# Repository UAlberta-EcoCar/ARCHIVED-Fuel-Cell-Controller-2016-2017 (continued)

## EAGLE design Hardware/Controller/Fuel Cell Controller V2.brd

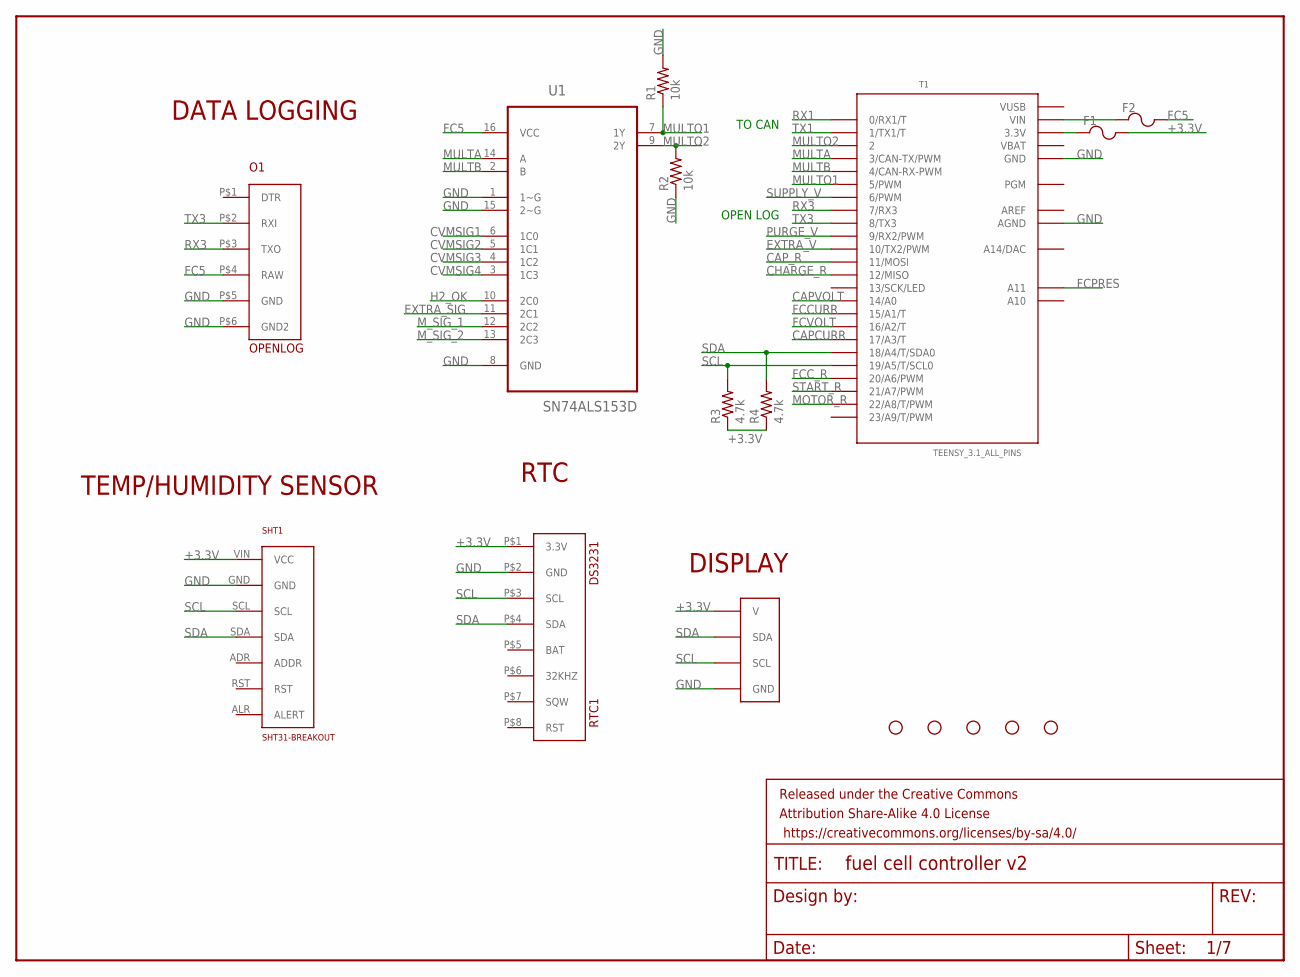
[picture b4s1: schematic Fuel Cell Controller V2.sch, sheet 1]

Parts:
F1, F2: POLYFUSE; 1206
FRAME1: FRAME-LETTERNO_PACKAGE; DUMMY
LCD1: LCD-BOARD
O1: OPENLOG
R1, R2: 10k; 0805
R3, R4: 4.7k; 0805
RTC1: DS3231
SHT1: SHT31-BREAKOUT
STANDOFF1, STANDOFF2, STANDOFF3, STANDOFF4, STANDOFF5: STAND-OFF
T1: TEENSY_3.1_ALL_PINS; TEENSY3-ALL_PINS
U1: SN74ALS153D; SOIC127P600X175-16N

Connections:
+3.3V: F1.2, LCD1.V, R3.1, R4.1, RTC1.P$1 (3.3V), SHT1.VIN (VCC); also elsewhere on the board
AREF: T1.AREF
CAPCURR: T1.17/A3 (17/A3/T); also elsewhere on the board
CAPVOLT: T1.14/A0; also elsewhere on the board
CAP_R: T1.11 (11/MOSI); also elsewhere on the board
CHARGE_R: T1.12 (12/MISO); also elsewhere on the board
CVMSIG1: U1.6 (1C0); also elsewhere on the board
CVMSIG2: U1.5 (1C1); also elsewhere on the board
CVMSIG3: U1.4 (1C2); also elsewhere on the board
CVMSIG4: U1.3 (1C3); also elsewhere on the board
EXTRA_SIG: U1.11 (2C1); also elsewhere on the board
EXTRA_V: T1.10 (10/TX2/PWM); also elsewhere on the board
FC5: F2.2, O1.P$4 (RAW), U1.16 (VCC); also elsewhere on the board
FCCURR: T1.15/A1 (15/A1/T); also elsewhere on the board
FCC_R: T1.20/A6 (20/A6/PWM); also elsewhere on the board
FCPRES: T1.A11; also elsewhere on the board
FCVOLT: T1.16/A2 (16/A2/T); also elsewhere on the board
GND: LCD1.GND1 (GND), LCD1.GND2 (GND), LCD1.GND3 (GND), LCD1.GND4 (GND), LCD1.GND5 (GND), LCD1.GND6 (GND), LCD1.GND7 (GND), LCD1.GND8 (GND), LCD1.GND9 (GND), LCD1.GND10 (GND), LCD1.GND11 (GND), LCD1.GND12 (GND), LCD1.GND13 (GND), O1.P$5 (GND), O1.P$6 (GND2), R1.2, R2.1, RTC1.P$2 (GND), SHT1.GND, T1.AGND, T1.GND, T1.GND1 (GND), U1.1 (1~G), U1.8 (GND), U1.15 (2~G); also elsewhere on the board
H2_OK: U1.10 (2C0); also elsewhere on the board
MOTOR_R: T1.22/A8 (22/A8/T/PWM); also elsewhere on the board
MULTA: T1.3 (3/CAN-TX/PWM), U1.14 (A)
MULTB: T1.4 (4/CAN-RX-PWM), U1.2 (B)
MULTO1: R1.1, T1.5 (5/PWM), U1.7 (1Y)
MULTO2: R2.2, T1.2, U1.9 (2Y)
M_SIG_1: U1.12 (2C2); also elsewhere on the board
M_SIG_2: U1.13 (2C3); also elsewhere on the board
unnamed: F2.1, T1.VIN
unnamed: F1.1, T1.3.3V, T1.3.3V1 (3.3V)
PURGE_V: T1.9 (9/RX2/PWM); also elsewhere on the board
RX1: T1.0 (0/RX1/T); also elsewhere on the board
RX3: O1.P$3 (TXO), T1.7 (7/RX3)
SCL: LCD1.SCL, R3.2, RTC1.P$3 (SCL), SHT1.SCL, T1.19/A5 (19/A5/T/SCL0); also elsewhere on the board
SDA: LCD1.SDA, R4.2, RTC1.P$4 (SDA), SHT1.SDA, T1.18/A4 (18/A4/T/SDA0); also elsewhere on the board
START_R: T1.21/A7 (21/A7/PWM); also elsewhere on the board
SUPPLY_V: T1.6 (6/PWM); also elsewhere on the board
TX1: T1.1 (1/TX1/T); also elsewhere on the board
TX3: O1.P$2 (RXI), T1.8 (8/TX3)
VBAT: T1.VBAT
VUSB: T1.VUSB

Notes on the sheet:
TO CAN
OPEN LOG
DISPLAY
DATA LOGGING
TEMP/HUMIDITY SENSOR
RTC

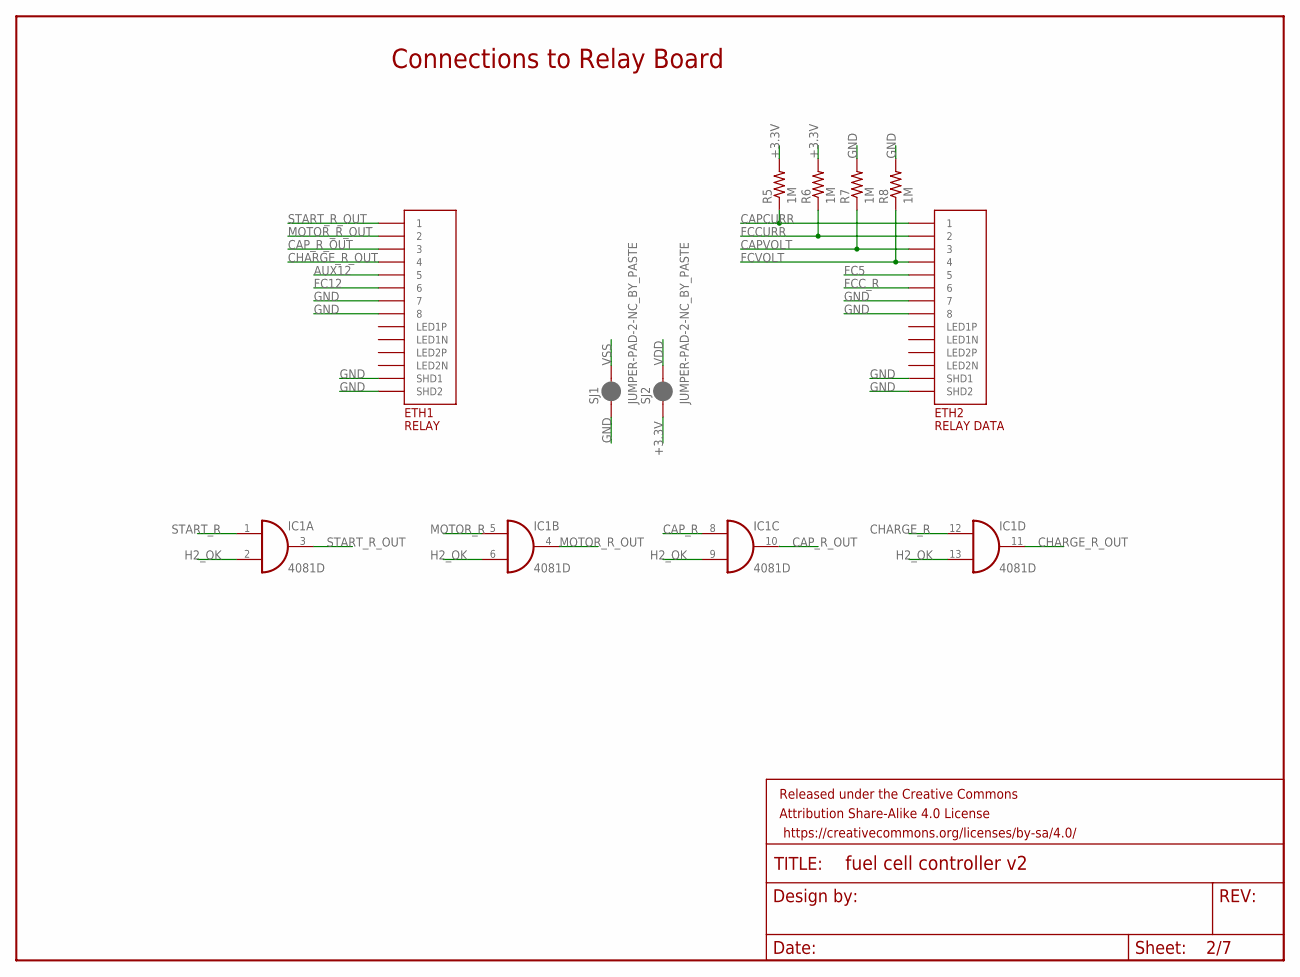
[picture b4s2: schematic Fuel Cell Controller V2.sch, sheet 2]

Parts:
ETH1: RELAY; A122645-ND
ETH2: RELAY DATA; A122645-ND
FRAME2: FRAME-LETTERNO_PACKAGE; DUMMY
IC1: 4081D; SO14
R5, R6, R7, R8: 1M; 0805
SJ1, SJ2: JUMPER-PAD-2-NC_BY_PASTE; PAD-JUMPER-2-NC_BY_PASTE_YES_SILK

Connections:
+3.3V: R5.2, R6.2, SJ2.1; also elsewhere on the board
AUX12: ETH1.P$5 (5); also elsewhere on the board
CAPCURR: ETH2.P$1 (1), R5.1; also elsewhere on the board
CAPVOLT: ETH2.P$3 (3), R7.1; also elsewhere on the board
CAP_R: IC1.8 (I0); also elsewhere on the board
CAP_R_OUT: ETH1.P$3 (3), IC1.10 (O)
CHARGE_R: IC1.12 (I0); also elsewhere on the board
CHARGE_R_OUT: ETH1.P$4 (4), IC1.11 (O)
FC5: ETH2.P$5 (5); also elsewhere on the board
FC12: ETH1.P$6 (6); also elsewhere on the board
FCCURR: ETH2.P$2 (2), R6.1; also elsewhere on the board
FCC_R: ETH2.P$6 (6); also elsewhere on the board
FCVOLT: ETH2.P$4 (4), R8.1; also elsewhere on the board
GND: ETH1.P$7 (7), ETH1.P$8 (8), ETH1.P$13 (SHD1), ETH1.P$14 (SHD2), ETH2.P$7 (7), ETH2.P$8 (8), ETH2.P$13 (SHD1), ETH2.P$14 (SHD2), R7.2, R8.2, SJ1.1; also elsewhere on the board
H2_OK: IC1.2 (I1), IC1.6 (I1), IC1.9 (I1), IC1.13 (I1); also elsewhere on the board
MOTOR_R: IC1.5 (I0); also elsewhere on the board
MOTOR_R_OUT: ETH1.P$2 (2), IC1.4 (O)
START_R: IC1.1 (I0); also elsewhere on the board
START_R_OUT: ETH1.P$1 (1), IC1.3 (O)
VDD: IC1.14 (VDD), SJ2.2
VSS: IC1.7 (VSS), SJ1.2

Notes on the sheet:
Connections to Relay Board

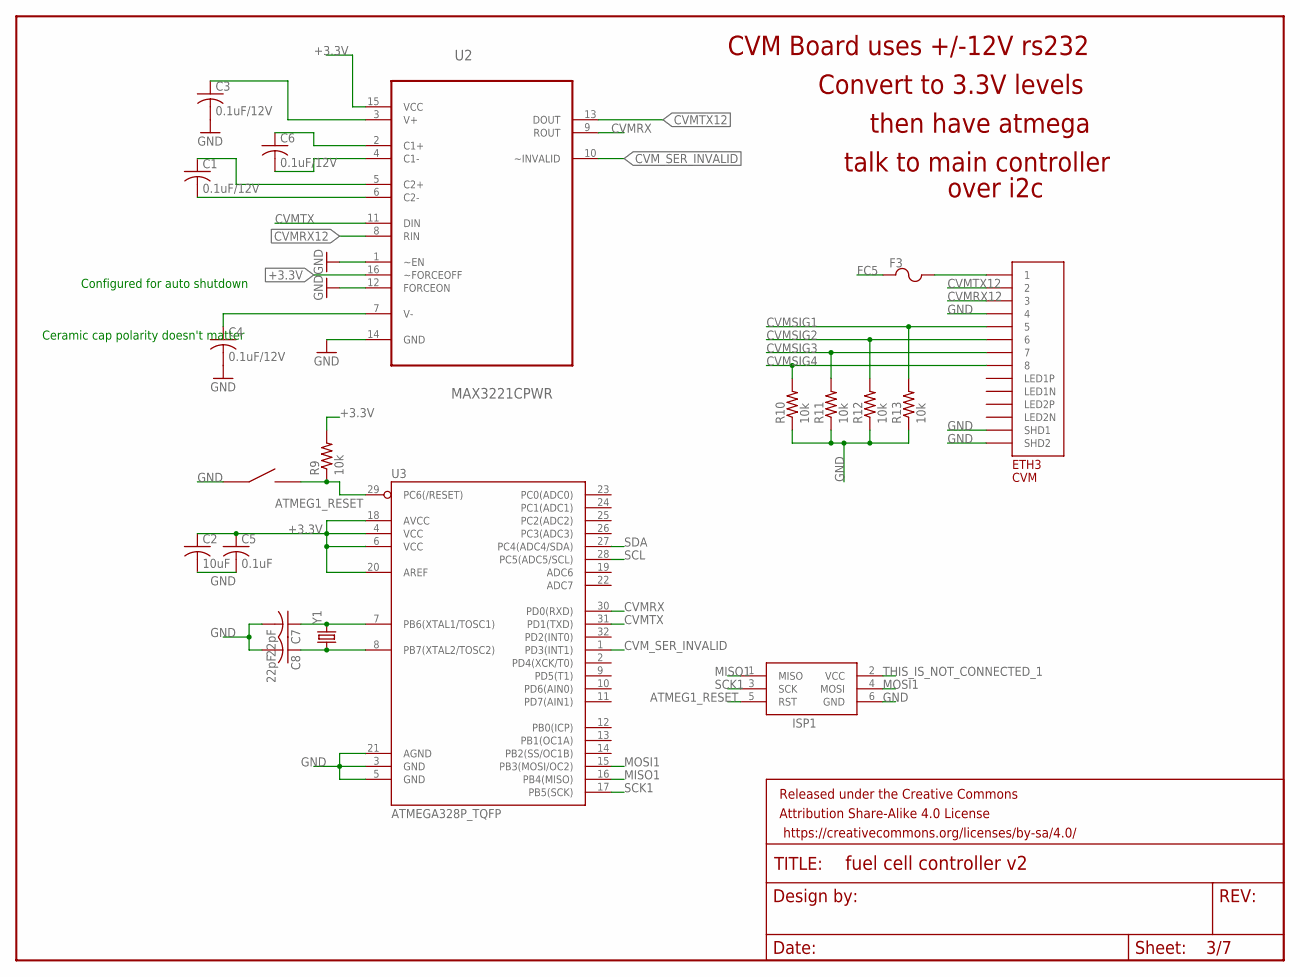
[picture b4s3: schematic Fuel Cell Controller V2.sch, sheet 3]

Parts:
C1, C3, C4, C6: 0.1uF/12V; C0805
C2: 10uF; C0603
C5: 0.1uF; C0603
C7, C8: 22pF; C0603
ETH3: CVM; A122645-ND
F3: POLYFUSE; 1206
FRAME3: FRAME-LETTERNO_PACKAGE; DUMMY
ISP1: AVRISP-BOX
R9: 10k; R0603
R10, R11, R12, R13: 10k; 0805
S1: EG4621CT-ND
U2: MAX3221CPWR; SOP65P640X120-16N
U3: ATMEGA328P_TQFP; TQFP32-08
Y1: CRYSTALHC49US; HC49US

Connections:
+3.3V: C2.1, C5.1, R9.2, U2.15 (VCC), U2.16 (~FORCEOFF), U3.4 (VCC), U3.6 (VCC), U3.18 (AVCC), U3.20 (AREF); also elsewhere on the board
ATMEG1_RESET: ISP1.5 (RST), R9.1, S1.P$3, S1.P$4, U3.29 (PC6(/RESET))
CVMRX: U2.9 (ROUT), U3.30 (PD0(RXD))
CVMRX12: ETH3.P$3 (3), U2.8 (RIN)
CVMSIG1: ETH3.P$5 (5), R13.2; also elsewhere on the board
CVMSIG2: ETH3.P$6 (6), R12.2; also elsewhere on the board
CVMSIG3: ETH3.P$7 (7), R11.2; also elsewhere on the board
CVMSIG4: ETH3.P$8 (8), R10.2; also elsewhere on the board
CVMTX: U2.11 (DIN), U3.31 (PD1(TXD))
CVMTX12: ETH3.P$2 (2), U2.13 (DOUT)
CVM_SER_INVALID: U2.10 (~INVALID), U3.1 (PD3(INT1))
FC5: F3.1; also elsewhere on the board
GND: C2.2, C3.2, C4.2, C5.2, C7.2, C8.2, ETH3.P$4 (4), ETH3.P$13 (SHD1), ETH3.P$14 (SHD2), ISP1.6 (GND), R10.1, R11.1, R12.1, R13.1, S1.P$1, S1.P$2, U2.1 (~EN), U2.12 (FORCEON), U2.14 (GND), U3.3 (GND), U3.5 (GND), U3.21 (AGND); also elsewhere on the board
MISO1: ISP1.1 (MISO), U3.16 (PB4(MISO))
MOSI1: ISP1.4 (MOSI), U3.15 (PB3(MOSI/OC2))
unnamed: C7.1, U3.7 (PB6(XTAL1/TOSC1)), Y1.2
unnamed: C8.1, U3.8 (PB7(XTAL2/TOSC2)), Y1.1
unnamed: ETH3.P$1 (1), F3.2
unnamed: C3.1, U2.3 (V+)
unnamed: C6.1, U2.2 (C1+)
unnamed: C6.2, U2.4 (C1-)
unnamed: C1.1, U2.5 (C2+)
unnamed: C1.2, U2.6 (C2-)
unnamed: C4.1, U2.7 (V-)
SCK1: ISP1.3 (SCK), U3.17 (PB5(SCK))
SCL: U3.28 (PC5(ADC5/SCL)); also elsewhere on the board
SDA: U3.27 (PC4(ADC4/SDA)); also elsewhere on the board
THIS_IS_NOT_CONNECTED_1: ISP1.2 (VCC)

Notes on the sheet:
Configured for auto shutdown
CVM Board uses +/-12V rs232
Convert to 3.3V levels
then have atmega
talk to main controller
over i2c
Ceramic cap polarity doesn't matter

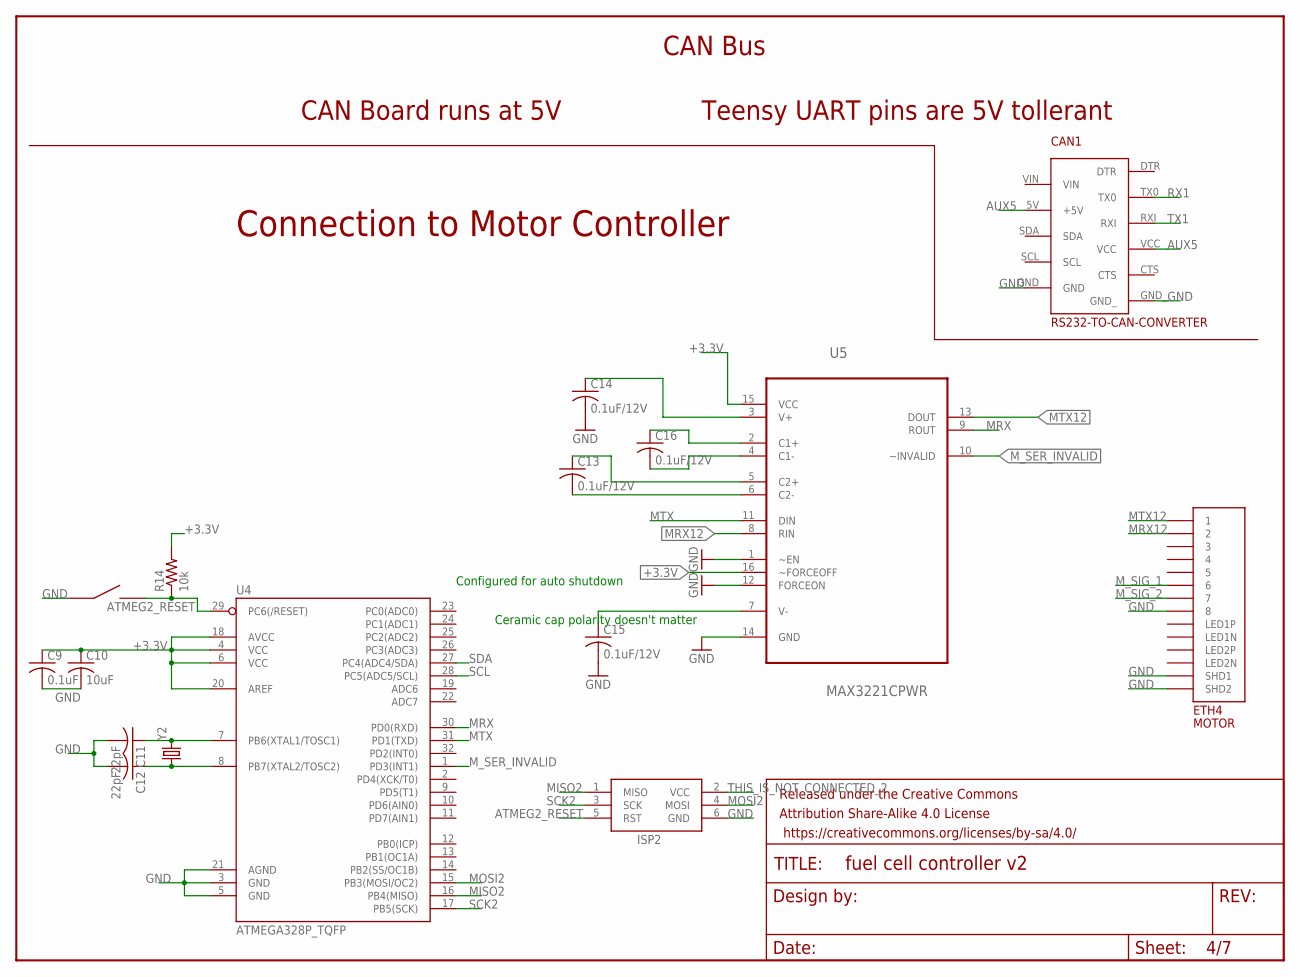
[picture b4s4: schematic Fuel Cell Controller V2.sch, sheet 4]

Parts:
C9: 0.1uF; C0603
C10: 10uF; C0603
C11, C12: 22pF; C0603
C13, C14, C15, C16: 0.1uF/12V; C0805
CAN1: RS232-TO-CAN-CONVERTER
ETH4: MOTOR; A122645-ND
FRAME4: FRAME-LETTERNO_PACKAGE; DUMMY
ISP2: AVRISP-BOX
R14: 10k; R0603
S2: EG4621CT-ND
U4: ATMEGA328P_TQFP; TQFP32-08
U5: MAX3221CPWR; SOP65P640X120-16N
Y2: CRYSTALHC49US; HC49US

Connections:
+3.3V: C9.1, C10.1, R14.2, U4.4 (VCC), U4.6 (VCC), U4.18 (AVCC), U4.20 (AREF), U5.15 (VCC), U5.16 (~FORCEOFF); also elsewhere on the board
ATMEG2_RESET: ISP2.5 (RST), R14.1, S2.P$3, S2.P$4, U4.29 (PC6(/RESET))
AUX5: CAN1.5V (+5V), CAN1.VCC; also elsewhere on the board
GND: C9.2, C10.2, C11.2, C12.2, C14.2, C15.2, CAN1.GND, CAN1.GND_, ETH4.P$8 (8), ETH4.P$13 (SHD1), ETH4.P$14 (SHD2), ISP2.6 (GND), S2.P$1, S2.P$2, U4.3 (GND), U4.5 (GND), U4.21 (AGND), U5.1 (~EN), U5.12 (FORCEON), U5.14 (GND); also elsewhere on the board
MISO2: ISP2.1 (MISO), U4.16 (PB4(MISO))
MOSI2: ISP2.4 (MOSI), U4.15 (PB3(MOSI/OC2))
MRX: U4.30 (PD0(RXD)), U5.9 (ROUT)
MRX12: ETH4.P$2 (2), U5.8 (RIN)
MTX: U4.31 (PD1(TXD)), U5.11 (DIN)
MTX12: ETH4.P$1 (1), U5.13 (DOUT)
M_SER_INVALID: U4.1 (PD3(INT1)), U5.10 (~INVALID)
M_SIG_1: ETH4.P$6 (6); also elsewhere on the board
M_SIG_2: ETH4.P$7 (7); also elsewhere on the board
unnamed: C11.1, U4.7 (PB6(XTAL1/TOSC1)), Y2.2
unnamed: C12.1, U4.8 (PB7(XTAL2/TOSC2)), Y2.1
unnamed: C14.1, U5.3 (V+)
unnamed: C16.1, U5.2 (C1+)
unnamed: C16.2, U5.4 (C1-)
unnamed: C13.1, U5.5 (C2+)
unnamed: C13.2, U5.6 (C2-)
unnamed: C15.1, U5.7 (V-)
RX1: CAN1.TX0; also elsewhere on the board
SCK2: ISP2.3 (SCK), U4.17 (PB5(SCK))
SCL: U4.28 (PC5(ADC5/SCL)); also elsewhere on the board
SDA: U4.27 (PC4(ADC4/SDA)); also elsewhere on the board
THIS_IS_NOT_CONNECTED_2: ISP2.2 (VCC)
TX1: CAN1.RXI; also elsewhere on the board

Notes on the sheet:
CAN Bus
CAN Board runs at 5V
Teensy UART pins are 5V tollerant
Connection to Motor Controller
Configured for auto shutdown
Ceramic cap polarity doesn't matter

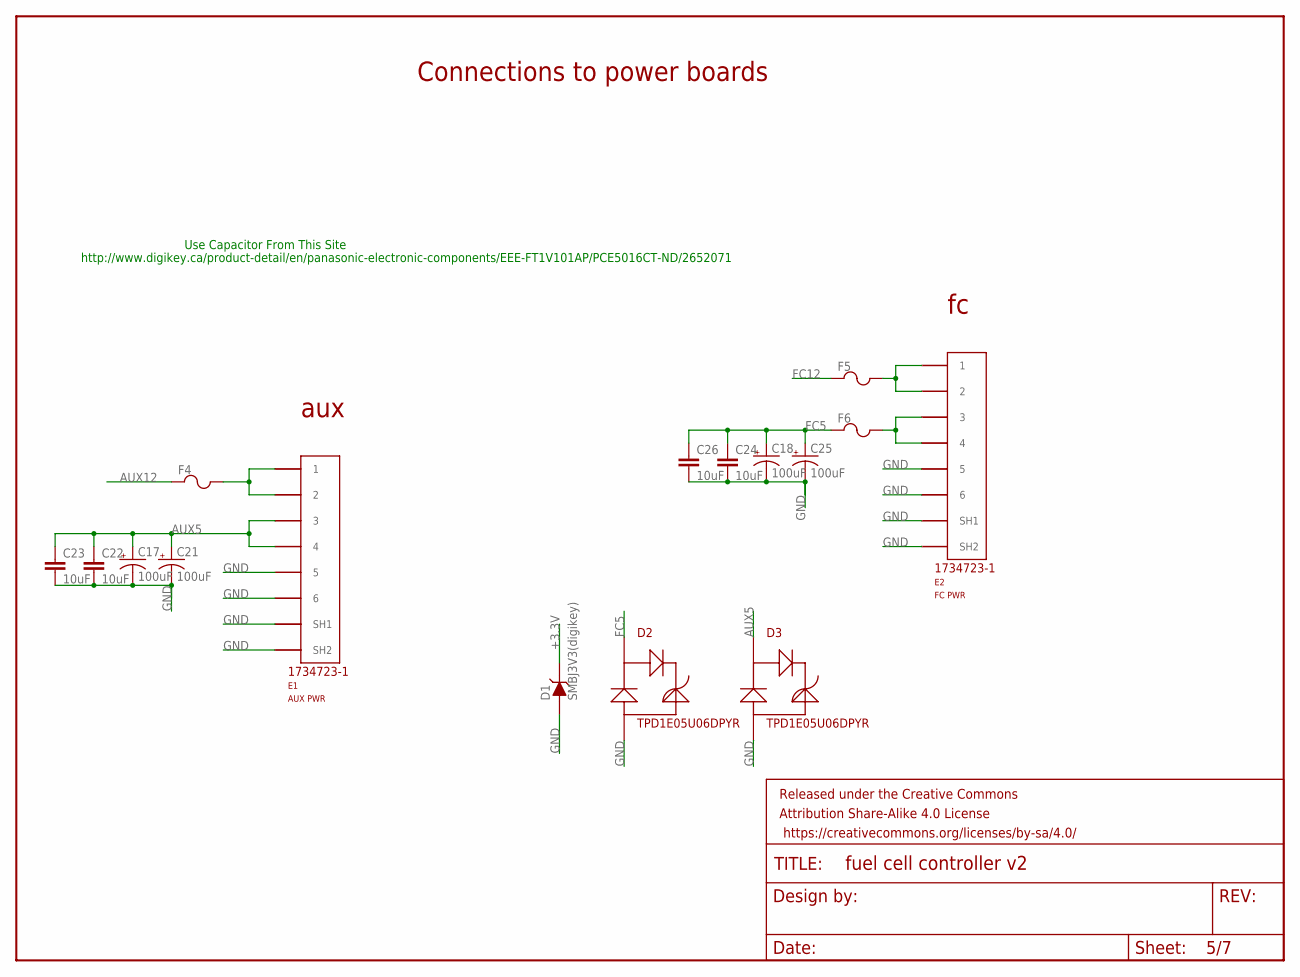
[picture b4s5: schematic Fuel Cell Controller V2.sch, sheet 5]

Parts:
C17, C18, C21, C25: 100uF; PANASONIC_D
C22, C23, C24, C26: 10uF; 0805
D1: SMBJ3V3(digikey); DO-214AB
D2, D3: TPD1E05U06DPYR; 2-XDFN
E1: AUX PWR; 1734723-1_RJ11
E2: FC PWR; 1734723-1_RJ11
F4, F5, F6: POLYFUSE; 1206
FRAME5: FRAME-LETTERNO_PACKAGE; DUMMY

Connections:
+3.3V: D1.C; also elsewhere on the board
AUX5: C17.+, C21.+, C22.1, C23.1, D3.P$1, E1.3, E1.4; also elsewhere on the board
AUX12: F4.1; also elsewhere on the board
FC5: C18.+, C24.1, C25.+, C26.1, D2.P$1, F6.1; also elsewhere on the board
FC12: F5.1; also elsewhere on the board
GND: C17.-, C18.-, C21.-, C22.2, C23.2, C24.2, C25.-, C26.2, D1.A, D2.P$2, D3.P$2, E1.5, E1.6, E1.SH1, E1.SH2, E2.5, E2.6, E2.SH1, E2.SH2; also elsewhere on the board
unnamed: E1.1, E1.2, F4.2
unnamed: E2.1, E2.2, F5.2
unnamed: E2.3, E2.4, F6.2

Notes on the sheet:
Connections to power boards
aux
Use Capacitor From This Site
http://www.digikey.ca/product-detail/en/panasonic-electronic-components/EEE-FT1V101AP/PCE5016CT-ND/2652071

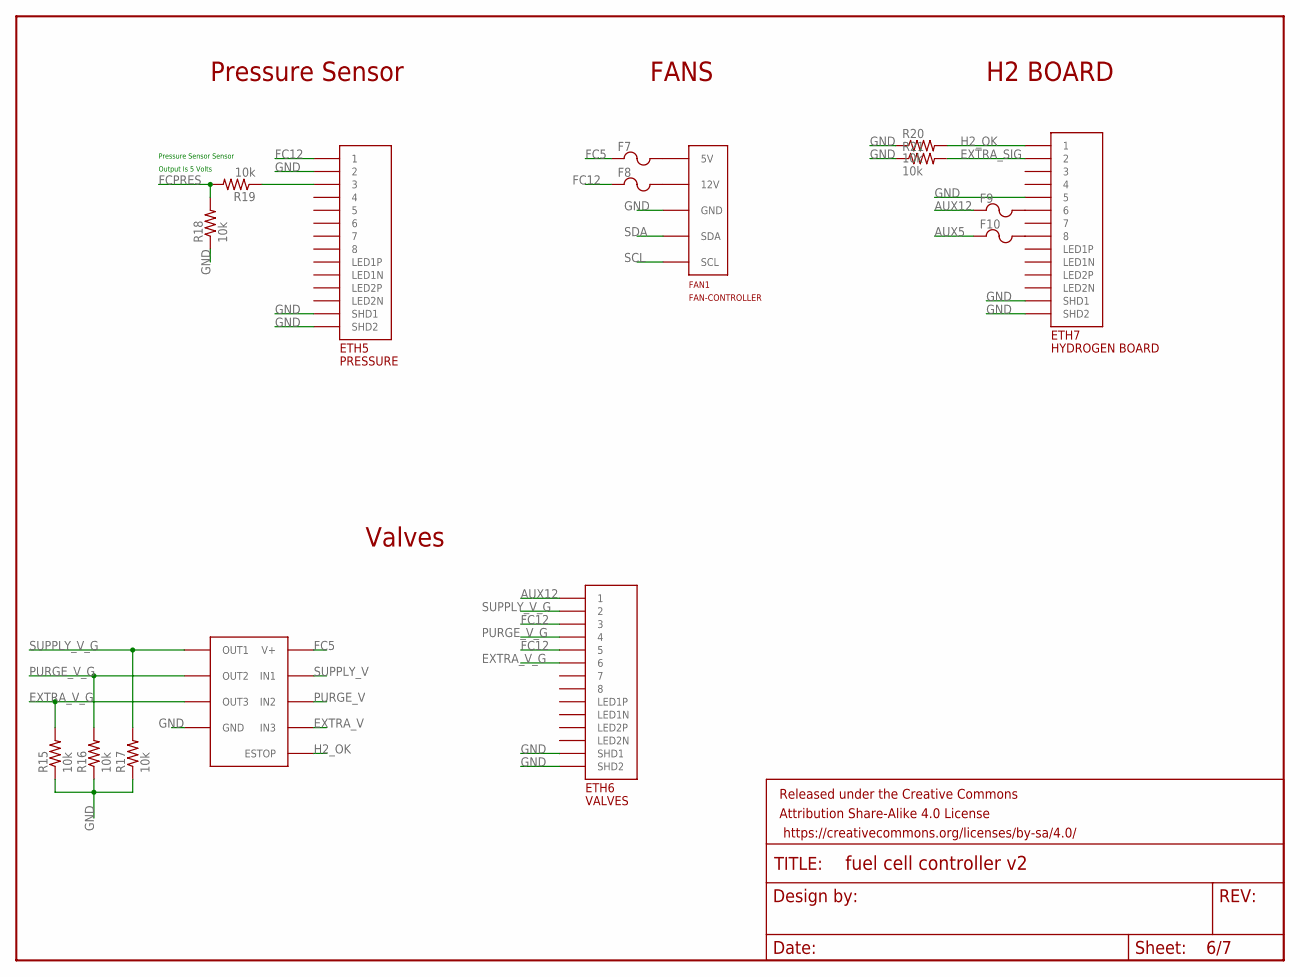
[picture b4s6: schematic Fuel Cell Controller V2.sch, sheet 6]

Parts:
ETH5: PRESSURE; A122645-ND
ETH6: VALVES; A122645-ND
ETH7: HYDROGEN BOARD; A122645-ND
F7, F8, F9, F10: POLYFUSE; 1206
FAN1: FAN-CONTROLLER
FRAME6: FRAME-LETTERNO_PACKAGE; DUMMY
M1: MOSFETBOARD; MOSFET-BOARD
R15, R16, R17, R18, R19: 10k; 0805
R20, R21: 10k; R0603

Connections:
AUX5: F10.1; also elsewhere on the board
AUX12: ETH6.P$1 (1), F9.1; also elsewhere on the board
EXTRA_SIG: ETH7.P$2 (2), R21.2; also elsewhere on the board
EXTRA_V: M1.IN3; also elsewhere on the board
EXTRA_V_G: ETH6.P$6 (6), M1.OUT3, R15.2
FC5: F7.1, M1.VDD (V+); also elsewhere on the board
FC12: ETH5.P$1 (1), ETH6.P$3 (3), ETH6.P$5 (5), F8.1; also elsewhere on the board
FCPRES: R18.2, R19.2; also elsewhere on the board
GND: ETH5.P$2 (2), ETH5.P$13 (SHD1), ETH5.P$14 (SHD2), ETH6.P$13 (SHD1), ETH6.P$14 (SHD2), ETH7.P$5 (5), ETH7.P$13 (SHD1), ETH7.P$14 (SHD2), FAN1.GND, FAN1.GND2 (GND), FAN1.GND3 (GND), M1.GND, M1.GND1 (GND), M1.GND2 (GND), M1.VSS (GND), R15.1, R16.1, R17.1, R18.1, R20.1, R21.1; also elsewhere on the board
H2_OK: ETH7.P$1 (1), M1.ESTOP, R20.2; also elsewhere on the board
unnamed: ETH7.P$6 (6), F9.2
unnamed: ETH7.P$8 (8), F10.2
unnamed: F7.2, FAN1.5 (5V), FAN1.5_2 (5V)
unnamed: F8.2, FAN1.12 (12V), FAN1.12_2 (12V), FAN1.12_3 (12V)
unnamed: ETH5.P$3 (3), R19.1
PURGE_V: M1.IN2; also elsewhere on the board
PURGE_V_G: ETH6.P$4 (4), M1.OUT2, R16.2
SCL: FAN1.SCL; also elsewhere on the board
SDA: FAN1.SDA; also elsewhere on the board
SUPPLY_V: M1.IN1; also elsewhere on the board
SUPPLY_V_G: ETH6.P$2 (2), M1.OUT1, R17.2

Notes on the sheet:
Valves
Pressure Sensor
FANS
H2 BOARD
Pressure Sensor Sensor
Output Is 5 Volts

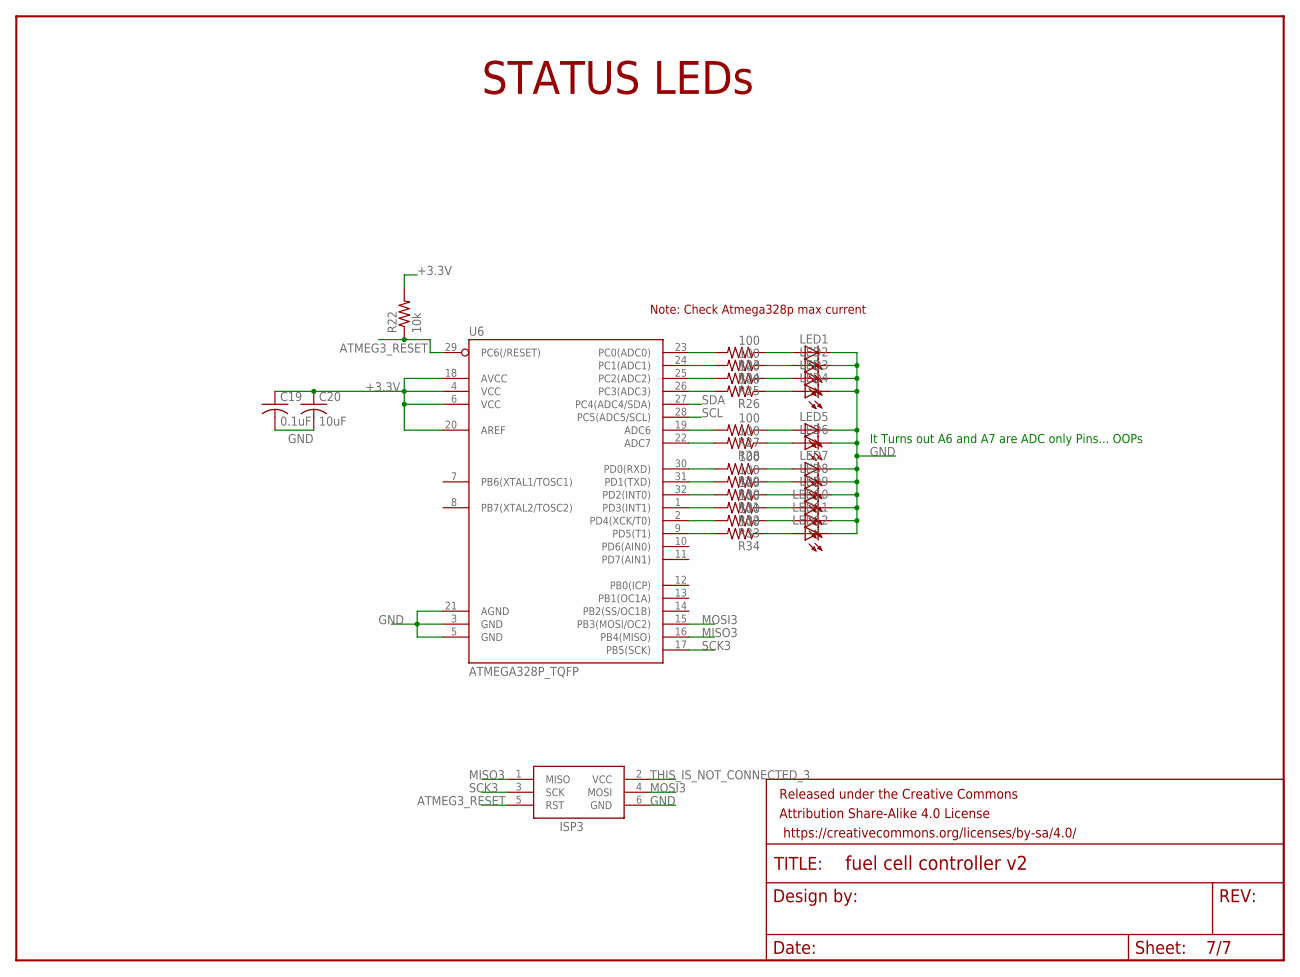
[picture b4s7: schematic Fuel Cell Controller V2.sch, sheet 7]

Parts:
C19: 0.1uF; C0603
C20: 10uF; C0603
FRAME7: FRAME-LETTERNO_PACKAGE; DUMMY
ISP3: AVRISP-BOX
LED1, LED2, LED3, LED4, LED5, LED6, LED7, LED8, LED9, LED10, LED11, LED12: LEDCHIPLED_0805; CHIPLED_0805
R22: 10k; R0603
R23, R24, R25, R26, R27, R28, R29, R30, R31, R32, R33, R34: 100; R0603
U6: ATMEGA328P_TQFP; TQFP32-08

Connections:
+3.3V: C19.1, C20.1, R22.2, U6.4 (VCC), U6.6 (VCC), U6.18 (AVCC), U6.20 (AREF); also elsewhere on the board
ATMEG3_RESET: ISP3.5 (RST), R22.1, U6.29 (PC6(/RESET))
GND: C19.2, C20.2, ISP3.6 (GND), LED1.C, LED2.C, LED3.C, LED4.C, LED5.C, LED6.C, LED7.C, LED8.C, LED9.C, LED10.C, LED11.C, LED12.C, U6.3 (GND), U6.5 (GND), U6.21 (AGND); also elsewhere on the board
MISO3: ISP3.1 (MISO), U6.16 (PB4(MISO))
MOSI3: ISP3.4 (MOSI), U6.15 (PB3(MOSI/OC2))
unnamed: R23.2, U6.23 (PC0(ADC0))
unnamed: R24.2, U6.24 (PC1(ADC1))
unnamed: R25.2, U6.25 (PC2(ADC2))
unnamed: R26.2, U6.26 (PC3(ADC3))
unnamed: R27.2, U6.19 (ADC6)
unnamed: R28.2, U6.22 (ADC7)
unnamed: R29.2, U6.30 (PD0(RXD))
unnamed: R30.2, U6.31 (PD1(TXD))
unnamed: R31.2, U6.32 (PD2(INT0))
unnamed: R32.2, U6.1 (PD3(INT1))
unnamed: R33.2, U6.2 (PD4(XCK/T0))
unnamed: R34.2, U6.9 (PD5(T1))
unnamed: LED12.A, R34.1
unnamed: LED11.A, R33.1
unnamed: LED10.A, R32.1
unnamed: LED9.A, R31.1
unnamed: LED8.A, R30.1
unnamed: LED7.A, R29.1
unnamed: LED6.A, R28.1
unnamed: LED5.A, R27.1
unnamed: LED4.A, R26.1
unnamed: LED3.A, R25.1
unnamed: LED2.A, R24.1
unnamed: LED1.A, R23.1
SCK3: ISP3.3 (SCK), U6.17 (PB5(SCK))
SCL: U6.28 (PC5(ADC5/SCL)); also elsewhere on the board
SDA: U6.27 (PC4(ADC4/SDA)); also elsewhere on the board
THIS_IS_NOT_CONNECTED_3: ISP3.2 (VCC)

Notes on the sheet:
STATUS LEDs
Note: Check Atmega328p max current
It Turns out A6 and A7 are ADC only Pins... OOPs

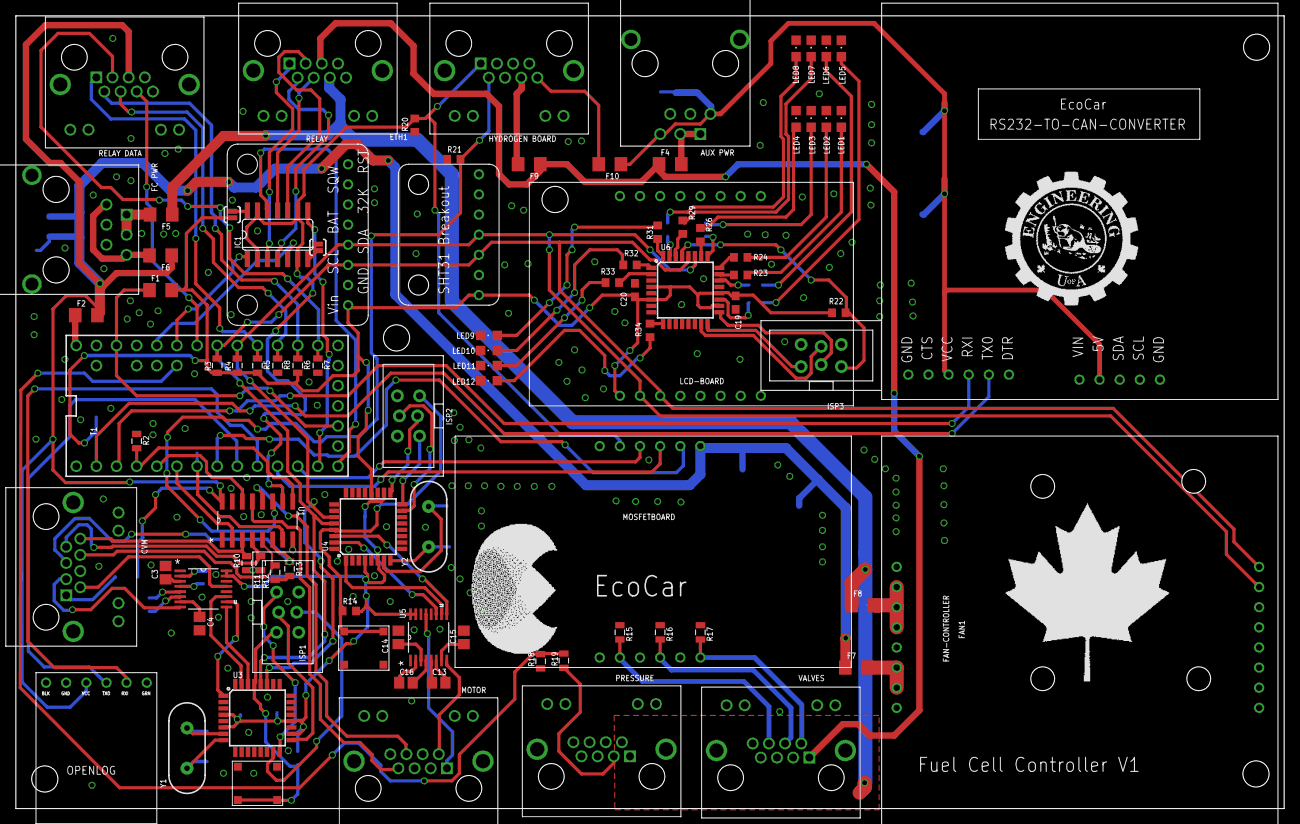
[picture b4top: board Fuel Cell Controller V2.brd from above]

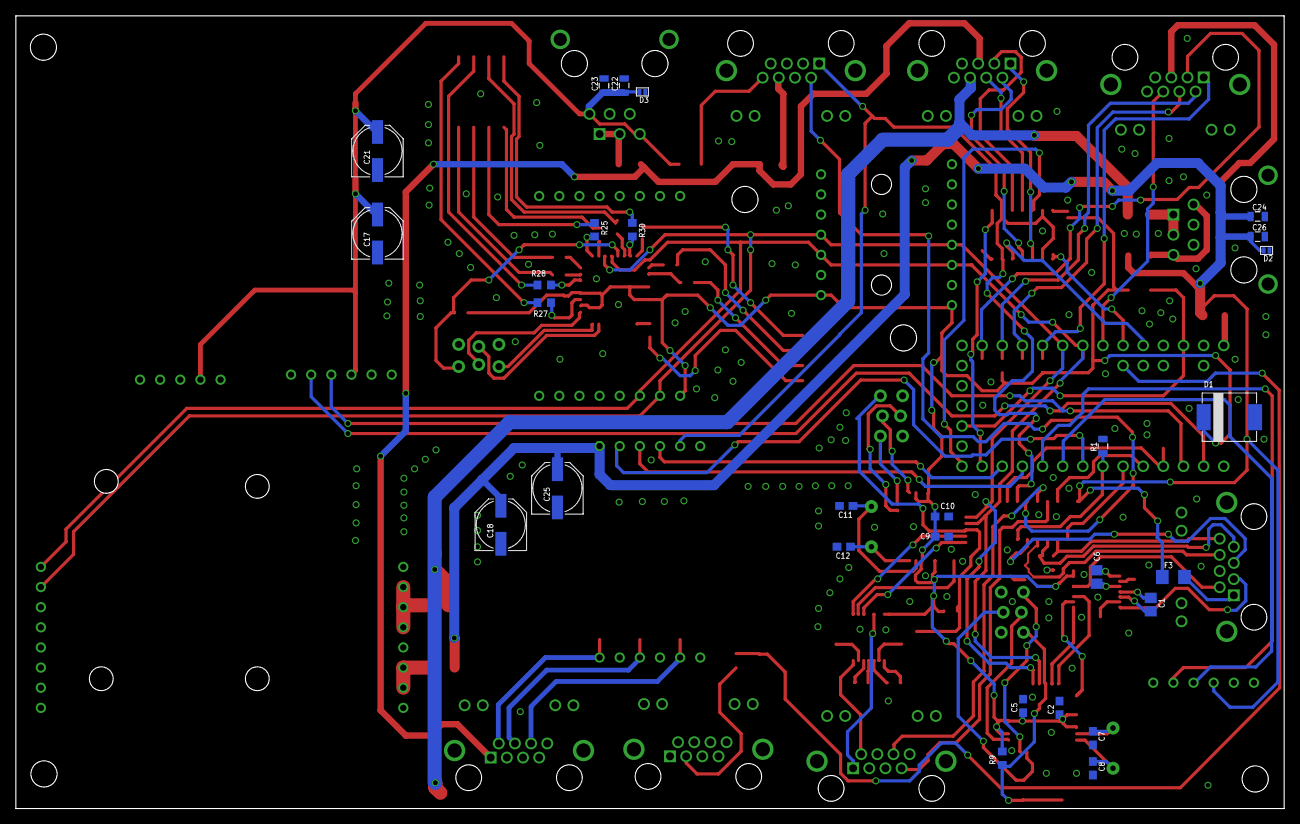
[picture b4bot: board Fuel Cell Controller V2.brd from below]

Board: 2 copper layers, 160.0 x 100.0 mm, 130 parts (28 on the bottom side), 119 nets.

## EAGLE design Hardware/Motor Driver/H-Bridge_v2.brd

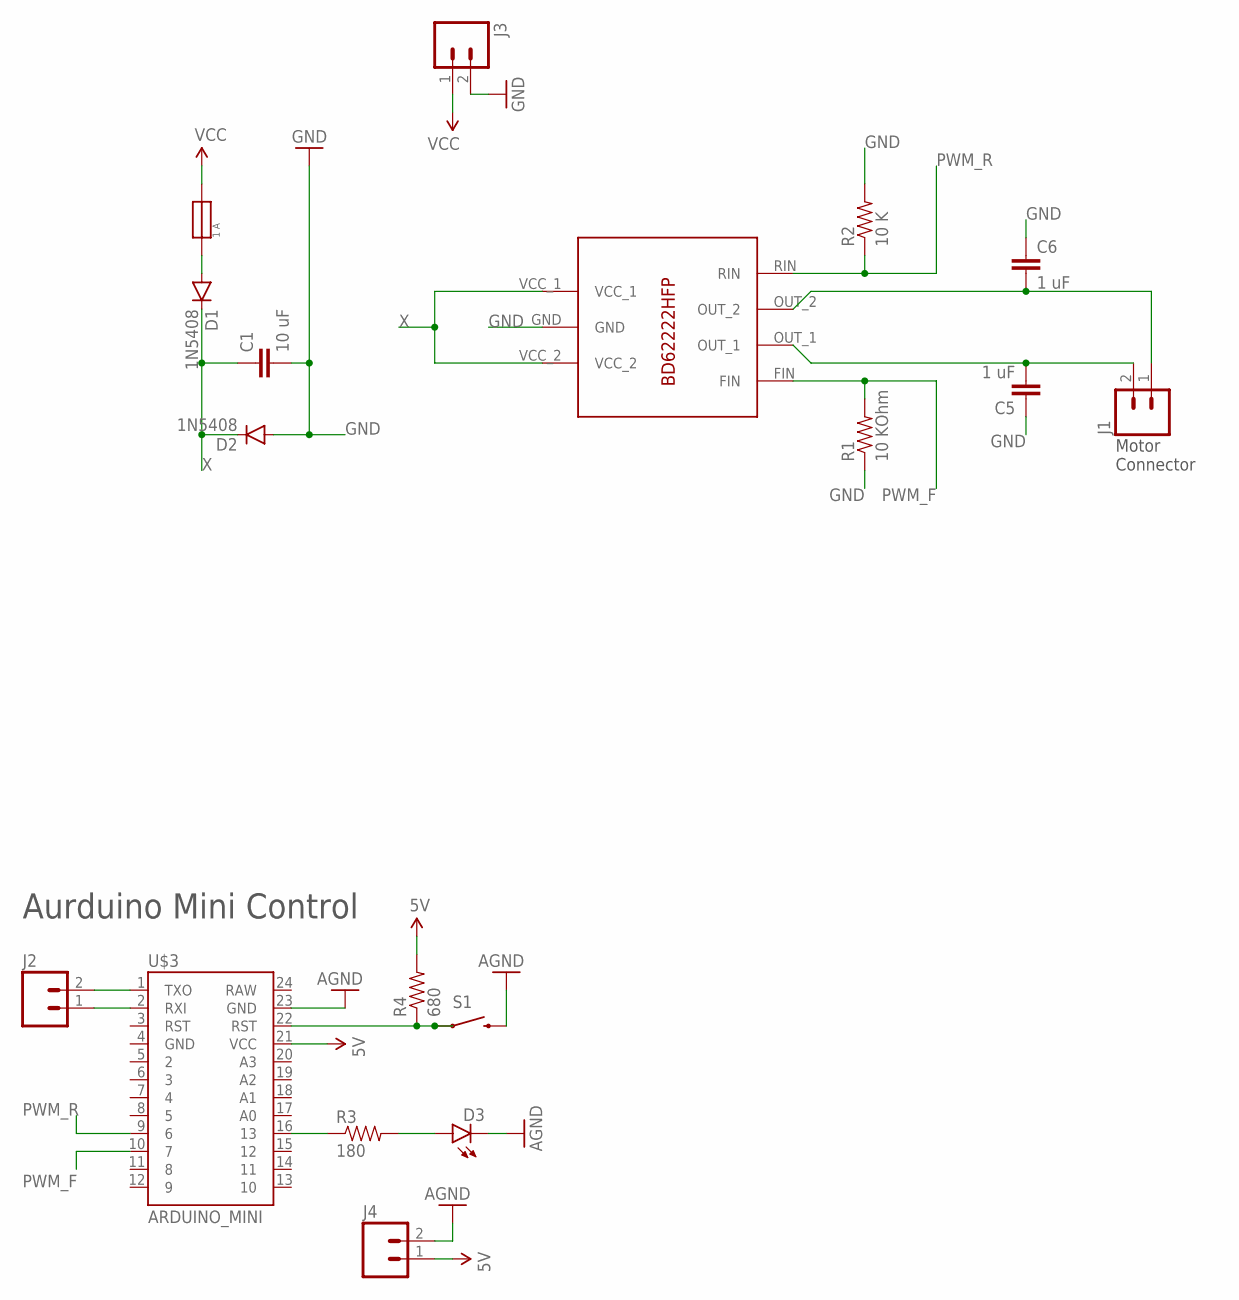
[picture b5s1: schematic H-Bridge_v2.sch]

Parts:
C1: 10 uF; 0805
C5, C6: 1 uF; 0805
D1, D2: 1N5408; DIODE-1N4148
D3: LED3MM
J1, J3, J4: M023.5MM; SCREWTERMINAL-3.5MM-2
J2: M02LOCK; 1X02_LOCK
R1: 10 KOhm; 1/6W-RES
R2: 10 K; 1/6W-RES
R3: 180; AXIAL-0.3
R4: 680; AXIAL-0.3
S1: SWITCH-MOMENTARY-2PTH; TACTILE-PTH
U$1: BD62222HFP
U$3: ARDUINO_MINI
U$8: 1 A; 5MM_PC_FUSE_HOLDER_KEYSTONE_ELEC

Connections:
5V: J4.1, R4.P$2 (2), U$3.21 (VCC)
AGND: D3.K (C), J4.2, S1.3 (2), U$3.23 (GND)
GND: C1.2, C5.1, C6.1, D2.A, J3.2, R1.1, R2.2, U$1.GND
unnamed: C5.2, J1.2, U$1.OUT_1
unnamed: C6.2, J1.1, U$1.OUT_2
unnamed: R3.P$1 (1), U$3.16 (13)
unnamed: D3.A, R3.P$2 (2)
unnamed: R4.P$1 (1), S1.1, U$3.22 (RST)
unnamed: J2.1, U$3.2 (RXI)
unnamed: J2.2, U$3.1 (TXO)
unnamed: D1.A, U$8.P$2
PWM_F: R1.2, U$1.FIN, U$3.10 (7)
PWM_R: R2.1, U$1.RIN, U$3.9 (6)
VCC: J3.1, U$8.P$1
X: C1.1, D1.C, D2.C, U$1.VCC_1, U$1.VCC_2

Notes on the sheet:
Motor Connector
Aurduino Mini Control

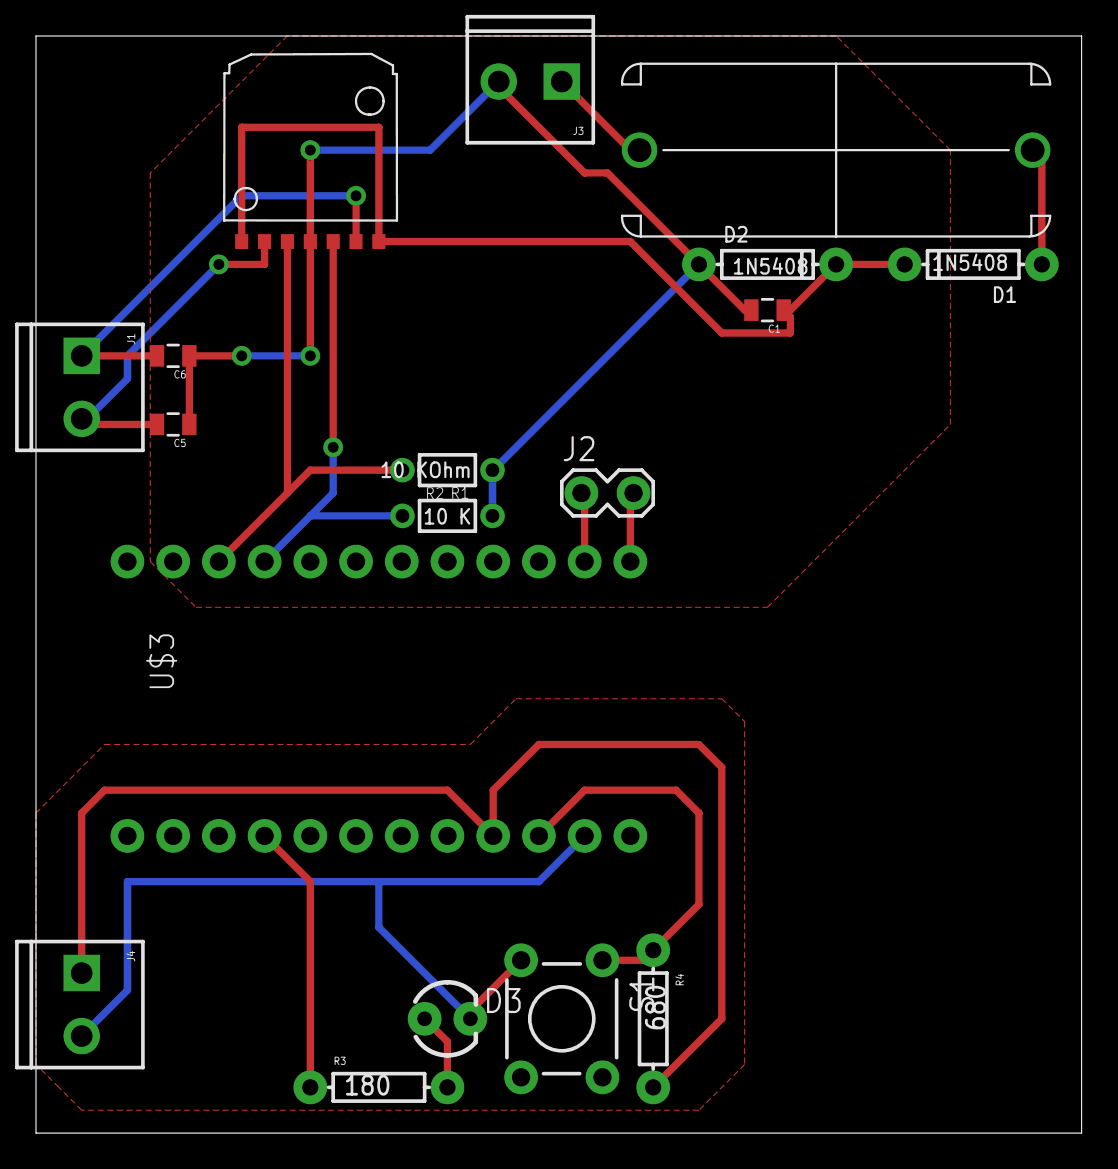
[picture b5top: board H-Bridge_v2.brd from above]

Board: 2 copper layers, 58.1 x 61.0 mm, 18 parts (0 on the bottom side), 15 nets.
